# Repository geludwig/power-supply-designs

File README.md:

# power-supply-designs
A small collection of power supply designs.

### SMPS WEIPU SP21
- Small 24mm x 14mm Switched Mode Power Supply which can be soldered into a waterproof WEIPU SP21 connector.
- 3A output, up to 40V input
- enable, overcurrent / overtemperature / reverse polarity protection
- 2-layer design

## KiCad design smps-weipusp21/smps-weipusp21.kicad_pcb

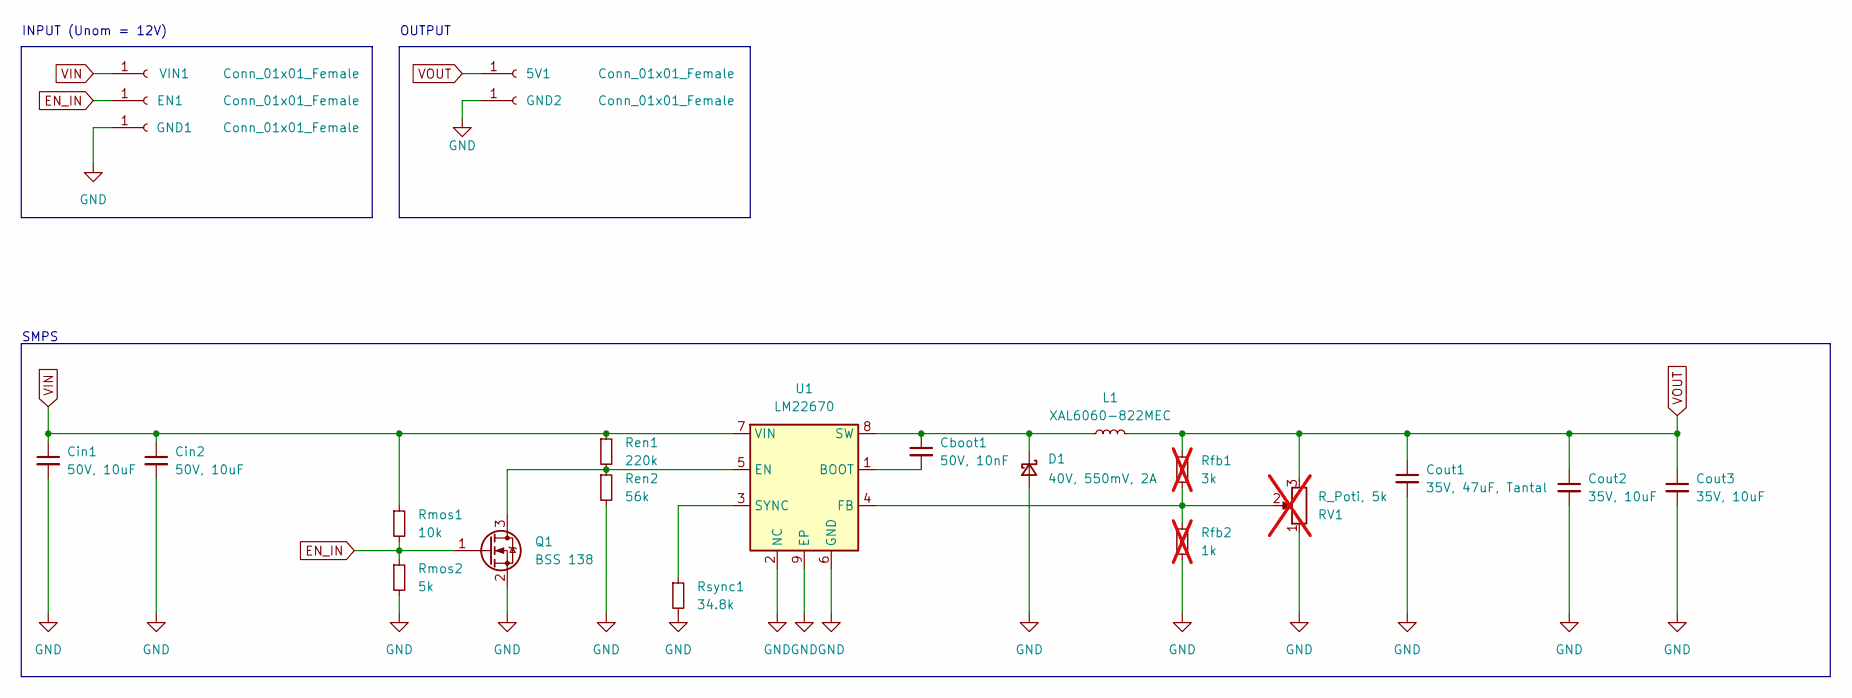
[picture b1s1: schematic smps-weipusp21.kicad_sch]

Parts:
5V1: Conn_01x01_Female; TestPoint_THTPad_D1.0mm_Drill0.5mm
Cboot1: 50V, 10nF; C_0603_1608Metric
Cin1, Cin2: 50V, 10uF; C_1210_3225Metric
Cout1: 35V, 47uF, Tantal; CP_EIA-3528-21_Kemet-B
Cout2, Cout3: 35V, 10uF; C_0805_2012Metric
D1: 40V, 550mV, 2A; D_SOD-128
EN1: Conn_01x01_Female; TestPoint_THTPad_D1.0mm_Drill0.5mm
GND1: Conn_01x01_Female; SolderWirePad_1x01_SMD_1x2mm
GND2: Conn_01x01_Female; TestPoint_THTPad_D1.0mm_Drill0.5mm
L1: XAL6060-822MEC; L_Coilcraft_XAL60xx_6.36x6.56mm
Q1: BSS 138; SOT-23W
RV1: R_Poti, 5k; Potentiometer_Bourns_TC33X_Vertical; not fitted
Ren1: 220k; R_0603_1608Metric
Ren2: 56k; R_0603_1608Metric
Rfb1: 3k; R_0603_1608Metric; not fitted
Rfb2: 1k; R_0603_1608Metric; not fitted
Rmos1: 10k; R_0603_1608Metric
Rmos2: 5k; R_0603_1608Metric
Rsync1: 34.8k; R_0603_1608Metric
U1: LM22670; TI_SO-PowerPAD-8
VIN1: Conn_01x01_Female; SolderWirePad_1x01_SMD_1x2mm

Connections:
EN_IN: EN1.1, Q1.1 (G), Rmos1.2, Rmos2.1
GND: Cin1.2, Cin2.2, Cout1.2, Cout2.2, Cout3.2, D1.2 (A), GND1.1, GND2.1, Q1.2 (S), RV1.1, Ren2.2, Rfb2.2, Rmos2.2, Rsync1.2, U1.2 (NC), U1.6 (GND), U1.9 (EP)
unnamed: Cboot1.1, D1.1 (K), L1.1, U1.8 (SW)
unnamed: Q1.3 (D), Ren1.2, Ren2.1, U1.5 (EN)
unnamed: Cboot1.2, U1.1 (BOOT)
unnamed: RV1.2, Rfb1.2, Rfb2.1, U1.4 (FB)
unnamed: Rsync1.1, U1.3 (SYNC)
VIN: Cin1.1, Cin2.1, Ren1.1, Rmos1.1, U1.7 (VIN), VIN1.1
VOUT: 5V1.1, Cout1.1, Cout2.1, Cout3.1, L1.2, RV1.3, Rfb1.1

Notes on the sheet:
OUTPUT
INPUT (Unom = 12V)
SMPS

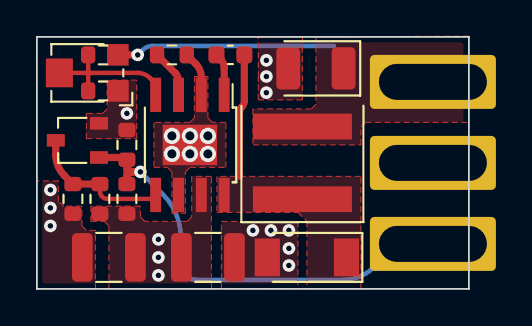
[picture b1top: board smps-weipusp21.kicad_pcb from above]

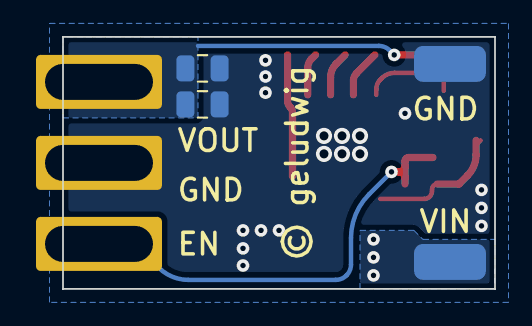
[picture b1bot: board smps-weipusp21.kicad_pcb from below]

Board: 2 copper layers, 24.0 x 14.0 mm, 23 parts (7 on the bottom side), 9 nets.

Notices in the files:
smps-weipusp21/smps-weipusp21.kicad_pcb:
© geludwig
